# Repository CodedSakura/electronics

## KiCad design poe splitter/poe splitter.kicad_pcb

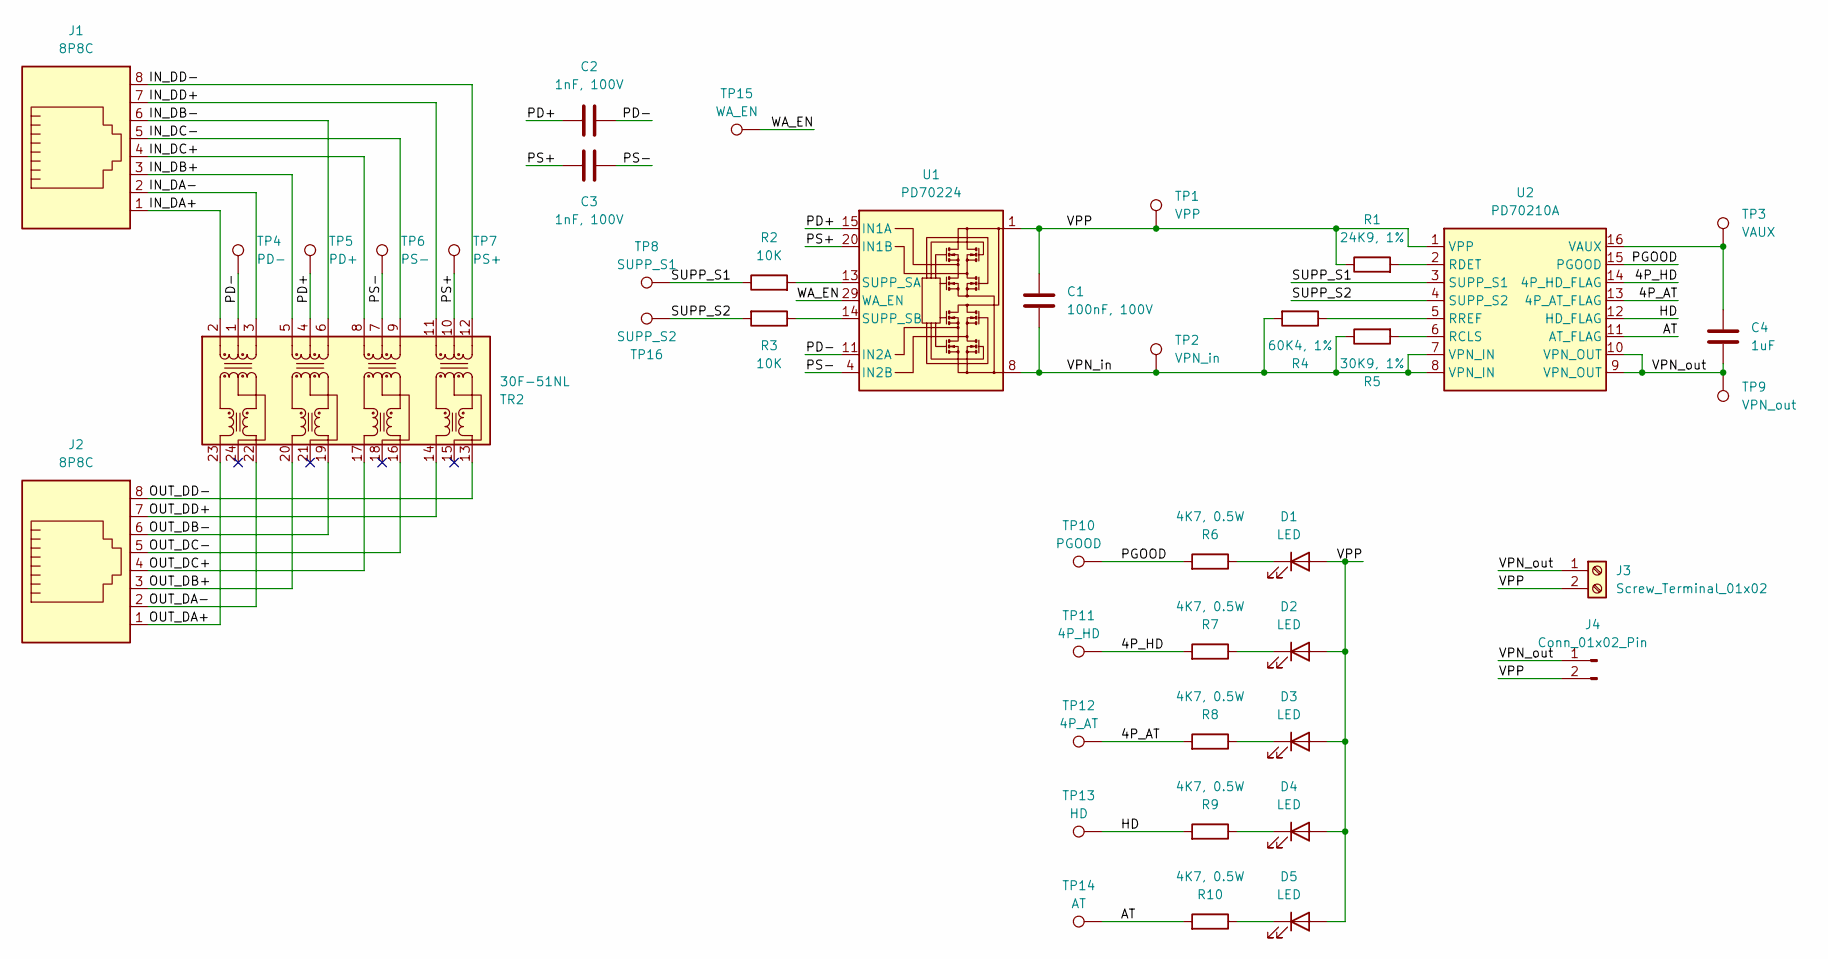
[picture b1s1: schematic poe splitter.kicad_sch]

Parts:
C1: 100nF, 100V; C_0805_2012Metric
C2, C3: 1nF, 100V; C_0805_2012Metric
C4: 1uF; C_0805_2012Metric
D1, D2, D3, D4, D5: LED; LED_0805_2012Metric
J1, J2: 8P8C; RJ45_Amphenol_54602-x08_Horizontal
J3: Screw_Terminal_01x02; TerminalBlock_Phoenix_MKDS-1,5-2_1x02_P5.00mm_Horizontal
J4: Conn_01x02_Pin; JST_VH_B2P-VH-B_1x02_P3.96mm_Vertical
R1: 24K9, 1%; R_0805_2012Metric
R2, R3: 10K; R_0805_2012Metric
R4: 60K4, 1%; R_0805_2012Metric
R5: 30K9, 1%; R_0805_2012Metric
R6, R7, R8, R9, R10: 4K7, 0.5W; R_0805_2012Metric
TP1: VPP; TestPoint_THTPad_1.0x1.0mm_Drill0.5mm
TP2: VPN_in; TestPoint_THTPad_1.0x1.0mm_Drill0.5mm
TP3: VAUX; TestPoint_THTPad_1.0x1.0mm_Drill0.5mm
TP4: PD-; TestPoint_THTPad_1.0x1.0mm_Drill0.5mm
TP5: PD+; TestPoint_THTPad_1.0x1.0mm_Drill0.5mm
TP6: PS-; TestPoint_THTPad_1.0x1.0mm_Drill0.5mm
TP7: PS+; TestPoint_THTPad_1.0x1.0mm_Drill0.5mm
TP8: SUPP_S1; TestPoint_THTPad_1.0x1.0mm_Drill0.5mm
TP9: VPN_out; TestPoint_THTPad_1.0x1.0mm_Drill0.5mm
TP10: PGOOD; TestPoint_THTPad_1.0x1.0mm_Drill0.5mm
TP11: 4P_HD; TestPoint_THTPad_1.0x1.0mm_Drill0.5mm
TP12: 4P_AT; TestPoint_THTPad_1.0x1.0mm_Drill0.5mm
TP13: HD; TestPoint_THTPad_1.0x1.0mm_Drill0.5mm
TP14: AT; TestPoint_THTPad_1.0x1.0mm_Drill0.5mm
TP15: WA_EN; TestPoint_THTPad_1.0x1.0mm_Drill0.5mm
TP16: SUPP_S2; TestPoint_THTPad_1.0x1.0mm_Drill0.5mm
TR2: 30F-51NL; Transformer_Ethernet_YDS_30F-51NL_SO-24_7.1x15.1mm
U1: PD70224; Microsemi_QFN-40-32-2EP_6x8mm_P0.5mm
U2: PD70210A; PD70210

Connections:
/4P_AT: R8.2, TP12.1, U2.13 (4P_AT_FLAG)
/4P_HD: R7.2, TP11.1, U2.14 (4P_HD_FLAG)
/AT: R10.2, TP14.1, U2.11 (AT_FLAG)
/HD: R9.2, TP13.1, U2.12 (HD_FLAG)
/IN_DA+: J1.1, TR2.2 (TD1+)
/IN_DA-: J1.2, TR2.3 (TD1-)
/IN_DB+: J1.3, TR2.5 (TD2+)
/IN_DB-: J1.6, TR2.6 (TD2-)
/IN_DC+: J1.4, TR2.8 (TD3+)
/IN_DC-: J1.5, TR2.9 (TD3-)
/IN_DD+: J1.7, TR2.11 (TD4+)
/IN_DD-: J1.8, TR2.12 (TD4-)
/OUT_DA+: J2.1, TR2.23 (MX1+)
/OUT_DA-: J2.2, TR2.22 (MX1-)
/OUT_DB+: J2.3, TR2.20 (MX2+)
/OUT_DB-: J2.6, TR2.19 (MX2-)
/OUT_DC+: J2.4, TR2.17 (MX3+)
/OUT_DC-: J2.5, TR2.16 (MX3-)
/OUT_DD+: J2.7, TR2.14 (MX4+)
/OUT_DD-: J2.8, TR2.13 (MX4-)
/PD+: C2.1, TP5.1, TR2.4 (CT), U1.15 (IN1A), U1.16 (IN1A), U1.27 (IN1A), U1.28 (IN1A)
/PD-: C2.2, TP4.1, TR2.1 (CT), U1.11 (IN2A), U1.12 (IN2A), U1.31 (IN2A), U1.32 (IN2A)
/PGOOD: R6.2, TP10.1, U2.15 (PGOOD)
/PS+: C3.1, TP7.1, TR2.10 (CT), U1.20 (IN1B), U1.21 (IN1B), U1.22 (IN1B), U1.23 (IN1B)
/PS-: C3.2, TP6.1, TR2.7 (CT), U1.4 (IN2B), U1.5 (IN2B), U1.6 (IN2B), U1.7 (IN2B)
/SUPP_S1: R2.1, TP8.1, U2.3 (SUPP_S1)
/SUPP_S2: R3.2, TP16.1, U2.4 (SUPP_S2)
/VPN_in: C1.2, R4.2, R5.1, TP2.1, U1.8, U1.9, U1.10, U1.17, U1.18, U1.19, U1.34, U2.7 (VPN_IN), U2.8 (VPN_IN)
/VPN_out: C4.2, J3.1, J4.1, TP9.1, U2.9 (VPN_OUT), U2.10 (VPN_OUT)
/VPP: C1.1, D1.2 (A), D2.2 (A), D3.2 (A), D4.2 (A), D5.2 (A), J3.2, J4.2, R1.1, TP1.1, U1.1, U1.2, U1.3, U1.24, U1.25, U1.26, U1.33, U2.1 (VPP)
/WA_EN: TP15.1, U1.29 (WA_EN)
unnamed: D1.1 (K), R6.1
unnamed: D2.1 (K), R7.1
unnamed: D3.1 (K), R8.1
unnamed: D4.1 (K), R9.1
unnamed: D5.1 (K), R10.1
unnamed: R2.2, U1.13 (SUPP_SA)
unnamed: R3.1, U1.14 (SUPP_SB)
unnamed: R5.2, U2.6 (RCLS)
unnamed: R1.2, U2.2 (RDET)
unnamed: R4.1, U2.5 (RREF)
unnamed: C4.1, TP3.1, U2.16 (VAUX)

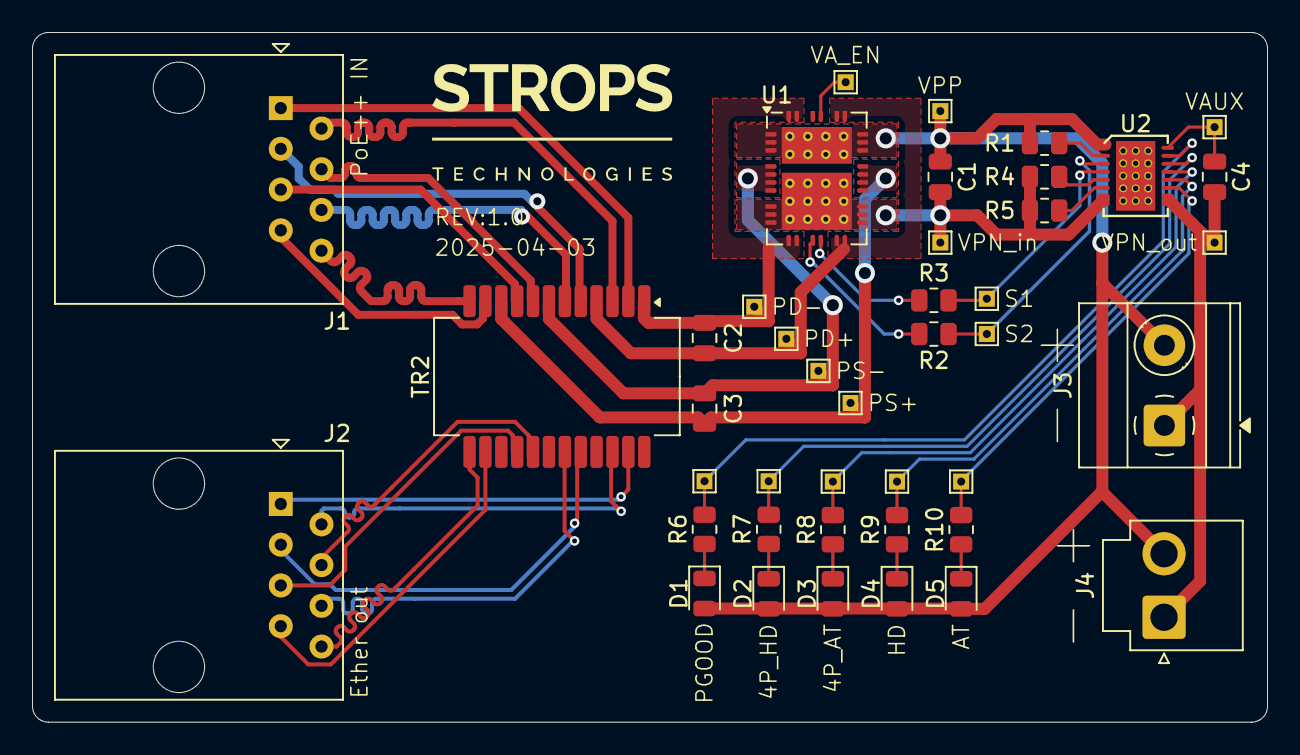
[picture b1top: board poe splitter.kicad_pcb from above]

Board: 2 copper layers, 77.0 x 43.0 mm, 42 parts (0 on the bottom side), 42 nets.

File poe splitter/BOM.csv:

Id+ADs-Designator+ADs-Footprint+ADs-Quantity+ADs-Designation+ADs-Supplier and ref+ADs-Price
1+ADs-C1+ADs-C+AF8-0805+AF8-2012Metric+ADs-1+ADs-100nF, 100V+ADs-JLCPCB C28233+ADs-
2+ADs-TP11+ADs-TestPoint+AF8-THTPad+AF8-1.0x1.0mm+AF8-Drill0.5mm+ADs-1+ADs-4P+AF8-HD+ADs-+AC0-+ADs-
3+ADs-R4+ADs-R+AF8-0805+AF8-2012Metric+ADs-1+ADs-60K4, 1+ACU-+ADs-JLCPCB C3016873+ADs-
4+ADs-J4+ADs-JST+AF8-VH+AF8-B2P+AC0-VH+AC0-B+AF8-1x02+AF8-P3.96mm+AF8-Vertical+ADs-1+ADs-Conn+AF8-01x02+AF8-Pin+ADs-JLCPCB C160315+ADs-
5+ADs-TR2+ADs-Transformer+AF8-Ethernet+AF8-YDS+AF8-30F+AC0-51NL+AF8-SO+AC0-24+AF8-7.1x15.1mm+ADs-1+ADs-30F+AC0-51NL+ADs-JLCPCB C123168+ADs-
6+ADs-R7,R8,R6,R10,R9+ADs-R+AF8-0805+AF8-2012Metric+ADs-5+ADs-4K7, 0.5W+ADs-JLCPCB C313926+ADs-
7+ADs-C4+ADs-C+AF8-0805+AF8-2012Metric+ADs-1+ADs-1uF+ADs-JLCPCB C105952+ADs-
8+ADs-D3,D4,D2,D5,D1+ADs-LED+AF8-0805+AF8-2012Metric+ADs-5+ADs-LED+ADs-JLCPCB C94741+ADs-
9+ADs-TP12+ADs-TestPoint+AF8-THTPad+AF8-1.0x1.0mm+AF8-Drill0.5mm+ADs-1+ADs-4P+AF8-AT+ADs-+AC0-+ADs-
10+ADs-U1+ADs-Microsemi+AF8-QFN+AC0-40+AC0-32+AC0-2EP+AF8-6x8mm+AF8-P0.5mm+ADs-1+ADs-PD70224+ADs-mouser 494+AC0-PD70224ILQ+AC0-TR+ADs-
11+ADs-J1,J2+ADs-RJ45+AF8-Amphenol+AF8-54602+AC0-x08+AF8-Horizontal+ADs-2+ADs-8P8C+ADs-mouser 649+AC0-54602+AC0-910LF+ADs-
12+ADs-R2,R3+ADs-R+AF8-0805+AF8-2012Metric+ADs-2+ADs-10K+ADs-JLCPCB C17414+ADs-
13+ADs-TP10+ADs-TestPoint+AF8-THTPad+AF8-1.0x1.0mm+AF8-Drill0.5mm+ADs-1+ADs-PGOOD+ADs-+AC0-+ADs-
14+ADs-TP7+ADs-TestPoint+AF8-THTPad+AF8-1.0x1.0mm+AF8-Drill0.5mm+ADs-1+ADs-PS+ADs-+AC0-+ADs-
15+ADs-J3+ADs-TerminalBlock+AF8-Phoenix+AF8-MKDS+AC0-1,5+AC0-2+AF8-1x02+AF8-P5.00mm+AF8-Horizontal+ADs-1+ADs-Screw+AF8-Terminal+AF8-01x02+ADs-mouser 651+AC0-1935161 +ADs-
16+ADs-TP3+ADs-TestPoint+AF8-THTPad+AF8-1.0x1.0mm+AF8-Drill0.5mm+ADs-1+ADs-VAUX+ADs-+AC0-+ADs-
17+ADs-TP9+ADs-TestPoint+AF8-THTPad+AF8-1.0x1.0mm+AF8-Drill0.5mm+ADs-1+ADs-VPN+AF8-out+ADs-+AC0-+ADs-
18+ADs-TP15+ADs-TestPoint+AF8-THTPad+AF8-1.0x1.0mm+AF8-Drill0.5mm+ADs-1+ADs-WA+AF8-EN+ADs-+AC0-+ADs-
19+ADs-TP5+ADs-TestPoint+AF8-THTPad+AF8-1.0x1.0mm+AF8-Drill0.5mm+ADs-1+ADs-PD+ADs-+AC0-+ADs-
20+ADs-R5+ADs-R+AF8-0805+AF8-2012Metric+ADs-1+ADs-30K9, 1+ACU-+ADs-JLCPCB C3016777+ADs-
21+ADs-U2+ADs-PD70210+ADs-1+ADs-PD70210A+ADs-mouser 494+AC0-PD70210AILD+AC0-TR+ADs-
22+ADs-R1+ADs-R+AF8-0805+AF8-2012Metric+ADs-1+ADs-24K9, 1+ACU-+ADs-JLCPCB C228658+ADs-
23+ADs-C3,C2+ADs-C+AF8-0805+AF8-2012Metric+ADs-2+ADs-1nF, 100V+ADs-JLCPCB C15177+ADs-
24+ADs-TP16+ADs-TestPoint+AF8-THTPad+AF8-1.0x1.0mm+AF8-Drill0.5mm+ADs-1+ADs-SUPP+AF8-S2+ADs-+AC0-+ADs-
25+ADs-TP8+ADs-TestPoint+AF8-THTPad+AF8-1.0x1.0mm+AF8-Drill0.5mm+ADs-1+ADs-SUPP+AF8-S1+ADs-+AC0-+ADs-
26+ADs-TP6+ADs-TestPoint+AF8-THTPad+AF8-1.0x1.0mm+AF8-Drill0.5mm+ADs-1+ADs-PS+AC0-+ADs-+AC0-+ADs-
27+ADs-TP1+ADs-TestPoint+AF8-THTPad+AF8-1.0x1.0mm+AF8-Drill0.5mm+ADs-1+ADs-VPP+ADs-+AC0-+ADs-
28+ADs-TP13+ADs-TestPoint+AF8-THTPad+AF8-1.0x1.0mm+AF8-Drill0.5mm+ADs-1+ADs-HD+ADs-+AC0-+ADs-
29+ADs-TP2+ADs-TestPoint+AF8-THTPad+AF8-1.0x1.0mm+AF8-Drill0.5mm+ADs-1+ADs-VPN+AF8-in+ADs-+AC0-+ADs-
30+ADs-TP14+ADs-TestPoint+AF8-THTPad+AF8-1.0x1.0mm+AF8-Drill0.5mm+ADs-1+ADs-AT+ADs-+AC0-+ADs-
31+ADs-TP4+ADs-TestPoint+AF8-THTPad+AF8-1.0x1.0mm+AF8-Drill0.5mm+ADs-1+ADs-PD+AC0-+ADs-+AC0-+ADs-

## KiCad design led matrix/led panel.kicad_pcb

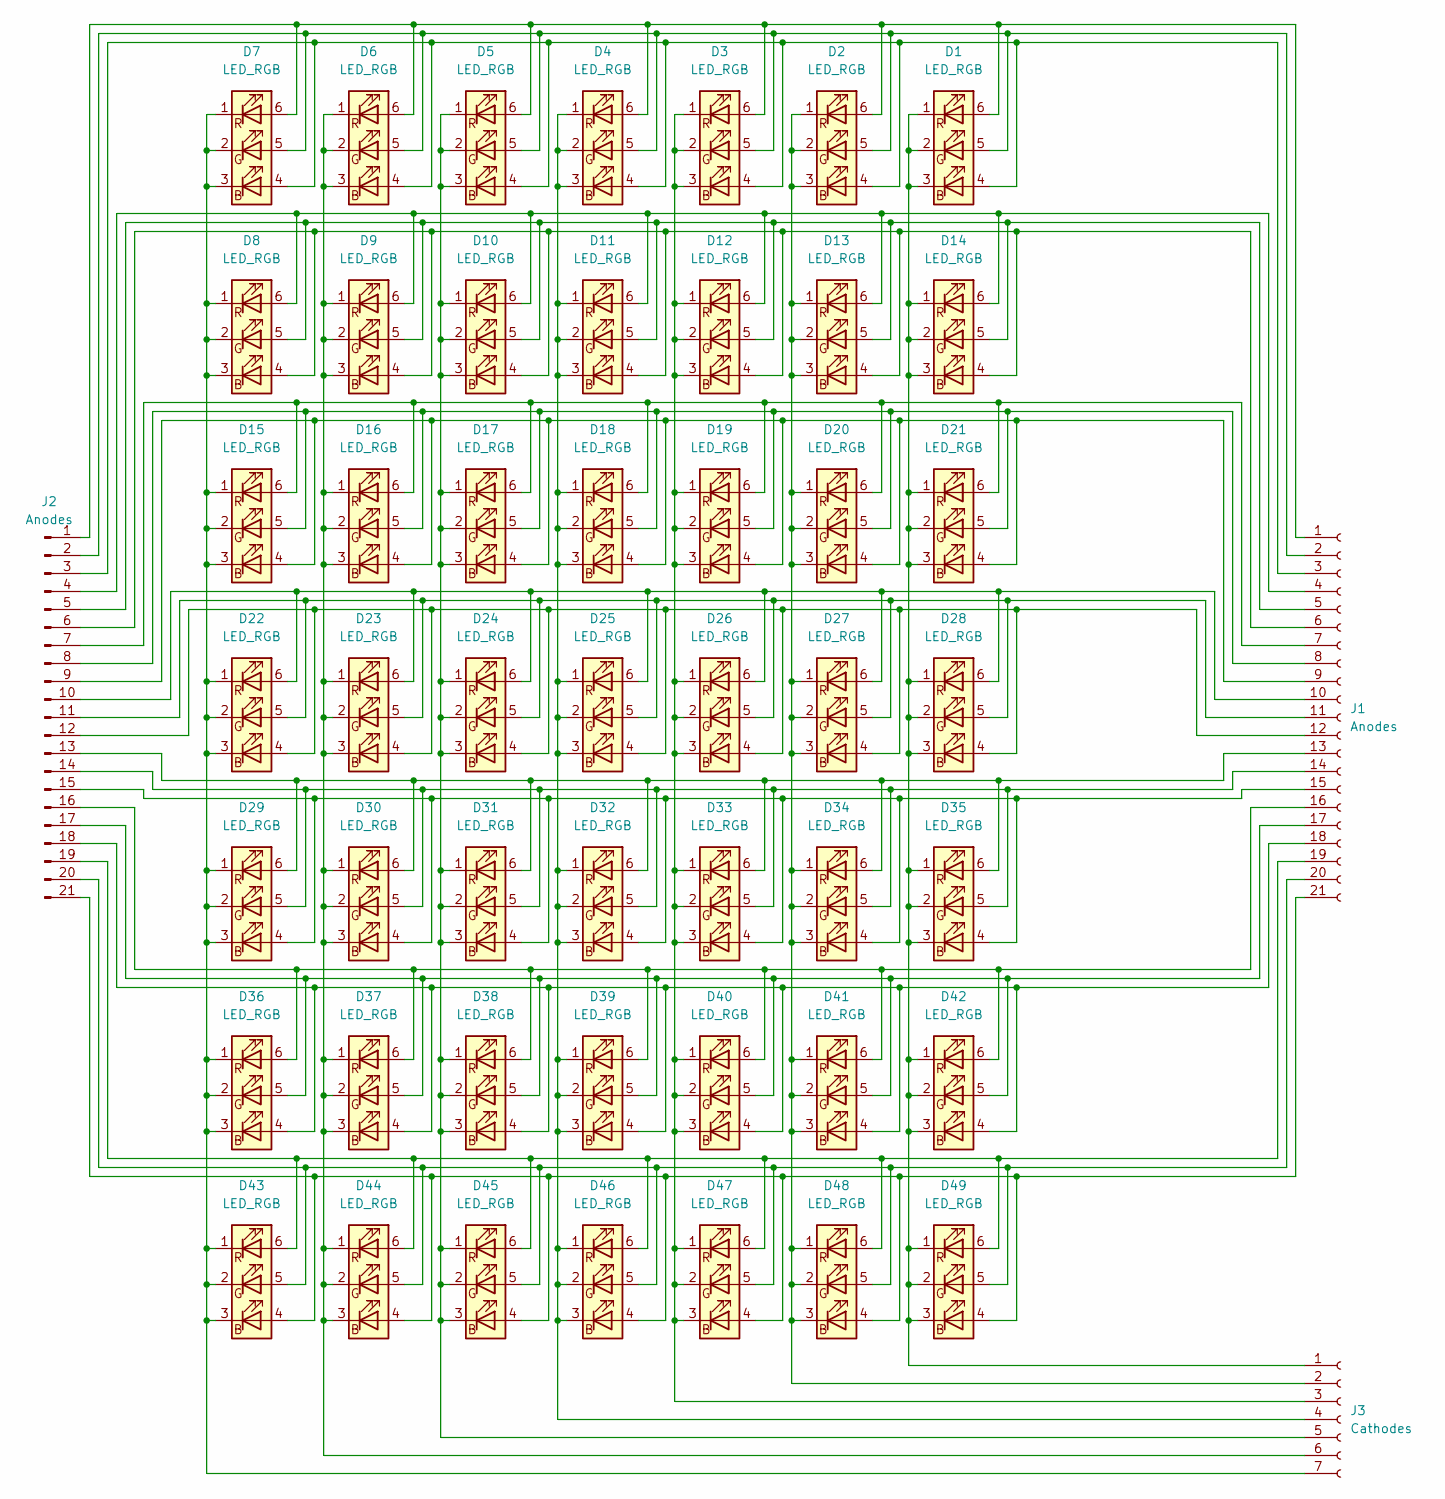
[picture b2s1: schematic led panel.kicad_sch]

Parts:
D1, D2, D3, D4, D5, D6, D7, D8, D9, D10, D11, D12, D13, D14, D15, D16, D17, D18, D19, D20, D21, D22, D23, D24, D25, D26, D27, D28, D29, D30, D31, D32, D33, D34, D35, D36, D37, D38, D39, D40, D41, D42, D43, D44, D45, D46, D47, D48, D49: LED_RGB; LED_RGB_5050-6
J1, J2: Anodes; Pin_1x21_P1.00mm_SMD
J3: Cathodes; Molex_200528-0070_1x07-1MP_P1.00mm_Horizontal

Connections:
unnamed: D1.4 (BA), D2.4 (BA), D3.4 (BA), D4.4 (BA), D5.4 (BA), D6.4 (BA), D7.4 (BA), J1.3, J2.3
unnamed: D1.1 (RK), D1.2 (GK), D1.3 (BK), D14.1 (RK), D14.2 (GK), D14.3 (BK), D21.1 (RK), D21.2 (GK), D21.3 (BK), D28.1 (RK), D28.2 (GK), D28.3 (BK), D35.1 (RK), D35.2 (GK), D35.3 (BK), D42.1 (RK), D42.2 (GK), D42.3 (BK), D49.1 (RK), D49.2 (GK), D49.3 (BK), J3.1
unnamed: D1.5 (GA), D2.5 (GA), D3.5 (GA), D4.5 (GA), D5.5 (GA), D6.5 (GA), D7.5 (GA), J1.2, J2.2
unnamed: D1.6 (RA), D2.6 (RA), D3.6 (RA), D4.6 (RA), D5.6 (RA), D6.6 (RA), D7.6 (RA), J1.1, J2.1
unnamed: D8.4 (BA), D9.4 (BA), D10.4 (BA), D11.4 (BA), D12.4 (BA), D13.4 (BA), D14.4 (BA), J1.6, J2.6
unnamed: D5.1 (RK), D5.2 (GK), D5.3 (BK), D10.1 (RK), D10.2 (GK), D10.3 (BK), D17.1 (RK), D17.2 (GK), D17.3 (BK), D24.1 (RK), D24.2 (GK), D24.3 (BK), D31.1 (RK), D31.2 (GK), D31.3 (BK), D38.1 (RK), D38.2 (GK), D38.3 (BK), D45.1 (RK), D45.2 (GK), D45.3 (BK), J3.5
unnamed: D8.5 (GA), D9.5 (GA), D10.5 (GA), D11.5 (GA), D12.5 (GA), D13.5 (GA), D14.5 (GA), J1.5, J2.5
unnamed: D8.6 (RA), D9.6 (RA), D10.6 (RA), D11.6 (RA), D12.6 (RA), D13.6 (RA), D14.6 (RA), J1.4, J2.4
unnamed: D4.1 (RK), D4.2 (GK), D4.3 (BK), D11.1 (RK), D11.2 (GK), D11.3 (BK), D18.1 (RK), D18.2 (GK), D18.3 (BK), D25.1 (RK), D25.2 (GK), D25.3 (BK), D32.1 (RK), D32.2 (GK), D32.3 (BK), D39.1 (RK), D39.2 (GK), D39.3 (BK), D46.1 (RK), D46.2 (GK), D46.3 (BK), J3.4
unnamed: D3.1 (RK), D3.2 (GK), D3.3 (BK), D12.1 (RK), D12.2 (GK), D12.3 (BK), D19.1 (RK), D19.2 (GK), D19.3 (BK), D26.1 (RK), D26.2 (GK), D26.3 (BK), D33.1 (RK), D33.2 (GK), D33.3 (BK), D40.1 (RK), D40.2 (GK), D40.3 (BK), D47.1 (RK), D47.2 (GK), D47.3 (BK), J3.3
unnamed: D2.1 (RK), D2.2 (GK), D2.3 (BK), D13.1 (RK), D13.2 (GK), D13.3 (BK), D20.1 (RK), D20.2 (GK), D20.3 (BK), D27.1 (RK), D27.2 (GK), D27.3 (BK), D34.1 (RK), D34.2 (GK), D34.3 (BK), D41.1 (RK), D41.2 (GK), D41.3 (BK), D48.1 (RK), D48.2 (GK), D48.3 (BK), J3.2
unnamed: D15.4 (BA), D16.4 (BA), D17.4 (BA), D18.4 (BA), D19.4 (BA), D20.4 (BA), D21.4 (BA), J1.9, J2.9
unnamed: D7.1 (RK), D7.2 (GK), D7.3 (BK), D8.1 (RK), D8.2 (GK), D8.3 (BK), D15.1 (RK), D15.2 (GK), D15.3 (BK), D22.1 (RK), D22.2 (GK), D22.3 (BK), D29.1 (RK), D29.2 (GK), D29.3 (BK), D36.1 (RK), D36.2 (GK), D36.3 (BK), D43.1 (RK), D43.2 (GK), D43.3 (BK), J3.7
unnamed: D15.5 (GA), D16.5 (GA), D17.5 (GA), D18.5 (GA), D19.5 (GA), D20.5 (GA), D21.5 (GA), J1.8, J2.8
unnamed: D15.6 (RA), D16.6 (RA), D17.6 (RA), D18.6 (RA), D19.6 (RA), D20.6 (RA), D21.6 (RA), J1.7, J2.7
unnamed: D6.1 (RK), D6.2 (GK), D6.3 (BK), D9.1 (RK), D9.2 (GK), D9.3 (BK), D16.1 (RK), D16.2 (GK), D16.3 (BK), D23.1 (RK), D23.2 (GK), D23.3 (BK), D30.1 (RK), D30.2 (GK), D30.3 (BK), D37.1 (RK), D37.2 (GK), D37.3 (BK), D44.1 (RK), D44.2 (GK), D44.3 (BK), J3.6
unnamed: D22.4 (BA), D23.4 (BA), D24.4 (BA), D25.4 (BA), D26.4 (BA), D27.4 (BA), D28.4 (BA), J1.12, J2.12
unnamed: D22.5 (GA), D23.5 (GA), D24.5 (GA), D25.5 (GA), D26.5 (GA), D27.5 (GA), D28.5 (GA), J1.11, J2.11
unnamed: D22.6 (RA), D23.6 (RA), D24.6 (RA), D25.6 (RA), D26.6 (RA), D27.6 (RA), D28.6 (RA), J1.10, J2.10
unnamed: D29.4 (BA), D30.4 (BA), D31.4 (BA), D32.4 (BA), D33.4 (BA), D34.4 (BA), D35.4 (BA), J1.15, J2.15
unnamed: D29.5 (GA), D30.5 (GA), D31.5 (GA), D32.5 (GA), D33.5 (GA), D34.5 (GA), D35.5 (GA), J1.14, J2.14
unnamed: D29.6 (RA), D30.6 (RA), D31.6 (RA), D32.6 (RA), D33.6 (RA), D34.6 (RA), D35.6 (RA), J1.13, J2.13
unnamed: D36.4 (BA), D37.4 (BA), D38.4 (BA), D39.4 (BA), D40.4 (BA), D41.4 (BA), D42.4 (BA), J1.18, J2.18
unnamed: D36.5 (GA), D37.5 (GA), D38.5 (GA), D39.5 (GA), D40.5 (GA), D41.5 (GA), D42.5 (GA), J1.17, J2.17
unnamed: D36.6 (RA), D37.6 (RA), D38.6 (RA), D39.6 (RA), D40.6 (RA), D41.6 (RA), D42.6 (RA), J1.16, J2.16
unnamed: D43.4 (BA), D44.4 (BA), D45.4 (BA), D46.4 (BA), D47.4 (BA), D48.4 (BA), D49.4 (BA), J1.21, J2.21
unnamed: D43.5 (GA), D44.5 (GA), D45.5 (GA), D46.5 (GA), D47.5 (GA), D48.5 (GA), D49.5 (GA), J1.20, J2.20
unnamed: D43.6 (RA), D44.6 (RA), D45.6 (RA), D46.6 (RA), D47.6 (RA), D48.6 (RA), D49.6 (RA), J1.19, J2.19

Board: 2 copper layers, 52 parts (3 on the bottom side), 28 nets, no tracks yet.

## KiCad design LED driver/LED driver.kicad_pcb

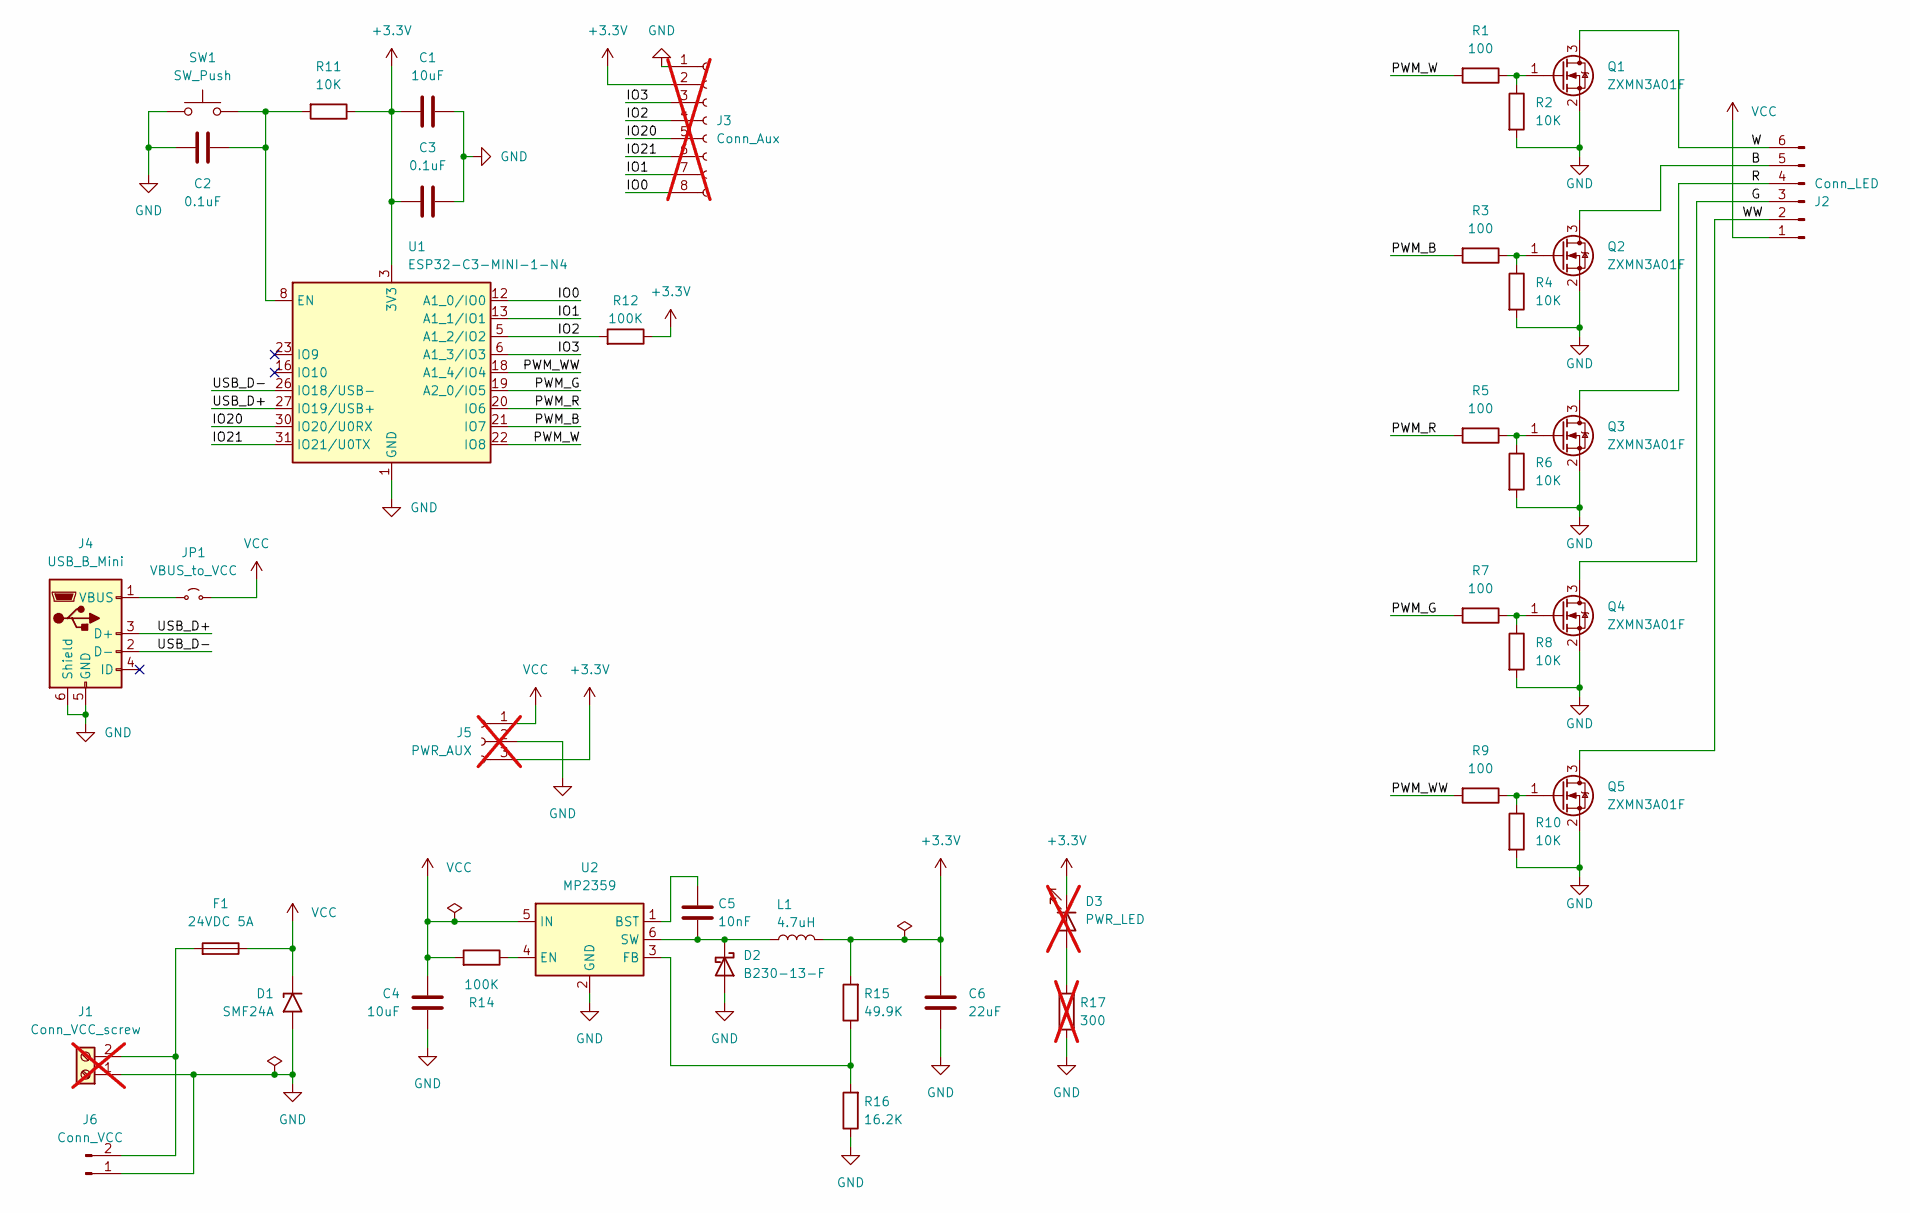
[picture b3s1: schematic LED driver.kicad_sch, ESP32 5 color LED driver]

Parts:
C1, C4: 10uF; C_0603_1608Metric
C2, C3: 0.1uF; C_0603_1608Metric
C5: 10nF; C_0603_1608Metric
C6: 22uF; C_0603_1608Metric
D1: SMF24A; D_SMF
D2: B230-13-F; D_SMB
D3: PWR_LED; D_0603_1608Metric_Pad1.05x0.95mm_HandSolder; not fitted
F1: 24VDC 5A; Fuse_1206_3216Metric_Pad1.42x1.75mm_HandSolder
J1: Conn_VCC_screw; TerminalBlock_Phoenix_MKDS-1,5-2_1x02_P5.00mm_Horizontal; not fitted
J2: Conn_LED; JST_VH_B6PS-VH_1x06_P3.96mm_Horizontal
J3: Conn_Aux; PinSocket_2x04_P2.54mm_Vertical; not fitted
J4: USB_B_Mini; USB_Mini-B_AdamTech_MUSB-B5-S-VT-TSMT-1_SMD_Vertical
J5: PWR_AUX; PinHeader_1x03_P2.54mm_Vertical; not fitted
J6: Conn_VCC; JST_VH_B2PS-VH_1x02_P3.96mm_Horizontal
JP1: VBUS_to_VCC; PinHeader_1x02_P2.54mm_Vertical
L1: 4.7uH; L_1210_3225Metric
Q1, Q2, Q3, Q4, Q5: ZXMN3A01F; SOT-23
R1, R3, R5, R7, R9: 100; R_0603_1608Metric
R2, R4, R6, R8, R10, R11: 10K; R_0603_1608Metric
R12, R14: 100K; R_0603_1608Metric
R15: 49.9K; R_0603_1608Metric
R16: 16.2K; R_0603_1608Metric
R17: 300; R_0603_1608Metric_Pad0.98x0.95mm_HandSolder; not fitted
SW1: SW_Push; SW_SPST_B3U-1000P
U1: ESP32-C3-MINI-1-N4; ESP32C3MINI1N4; Mouser Part Number 356-ESP32-C3-MINI1N4
U2: MP2359; TSOT-23-6

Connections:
+3.3V: C1.2, C3.2, C6.1, D3.1 (K), J3.2, J5.3, L1.2, R11.1, R12.1, R15.2, U1.3 (3V3)
/B: J2.5, Q2.3 (D)
/G: J2.3, Q4.3 (D)
/IO0: J3.8, U1.12 (A1_0/IO0)
/IO1: J3.7, U1.13 (A1_1/IO1)
/IO2: J3.4, R12.2, U1.5 (A1_2/IO2)
/IO3: J3.3, U1.6 (A1_3/IO3)
/IO20: J3.5, U1.30 (IO20/U0RX)
/IO21: J3.6, U1.31 (IO21/U0TX)
/PWM_B: R3.2, U1.21 (IO7)
/PWM_G: R7.2, U1.19 (A2_0/IO5)
/PWM_R: R5.2, U1.20 (IO6)
/PWM_W: R1.2, U1.22 (IO8)
/PWM_WW: R9.2, U1.18 (A1_4/IO4)
/R: J2.4, Q3.3 (D)
/USB_D+: J4.3 (D+), U1.27 (IO19/USB+)
/USB_D-: J4.2 (D-), U1.26 (IO18/USB-)
/W: J2.6, Q1.3 (D)
/WW: J2.2, Q5.3 (D)
GND: C1.1, C2.1, C3.1, C4.2, C6.2, D1.2 (A2), D2.2 (A), J1.1, J3.1, J4.5 (GND), J4.6 (Shield), J5.2, J6.1, Q1.2 (S), Q2.2 (S), Q3.2 (S), Q4.2 (S), Q5.2 (S), R2.2, R4.2, R6.2, R8.2, R10.2, R16.1, R17.1, SW1.1, U1.1 (GND), U1.2 (GND_2), U1.11 (GND_3), U1.14 (GND_4), U1.36 (GND_5), U1.37 (GND_6), U1.38 (GND_7), U1.39 (GND_8), U1.40 (GND_9), U1.41 (GND_10), U1.42 (GND_11), U1.43 (GND_12), U1.44 (GND_13), U1.45 (GND_14), U1.46 (GND_15), U1.47 (GND_16), U1.48 (GND_17), U1.49 (GND_18), U1.50 (GND_19), U1.51 (GND_20), U1.52 (GND_21), U1.53 (GND_22), U1.54 (GND_23), U1.55 (GND_24), U1.56 (GND_25), U1.57 (GND_26), U1.58 (GND_27), U1.59 (GND_28), U1.60 (GND_29), U1.61 (GND_30), U2.2 (GND)
unnamed: C5.2, D2.1 (K), L1.1, U2.6 (SW)
unnamed: D3.2 (A), R17.2
unnamed: F1.2, J1.2, J6.2
unnamed: J4.1 (VBUS), JP1.1 (A)
unnamed: Q1.1 (G), R1.1, R2.1
unnamed: Q2.1 (G), R3.1, R4.1
unnamed: Q3.1 (G), R5.1, R6.1
unnamed: Q4.1 (G), R7.1, R8.1
unnamed: Q5.1 (G), R9.1, R10.1
unnamed: C2.2, R11.2, SW1.2, U1.8 (EN)
unnamed: C5.1, U2.1 (BST)
unnamed: R14.1, U2.4 (EN)
unnamed: R15.1, R16.2, U2.3 (FB)
VCC: C4.1, D1.1 (A1), F1.1, J2.1, J5.1, JP1.2 (B), R14.2, U2.5 (IN)

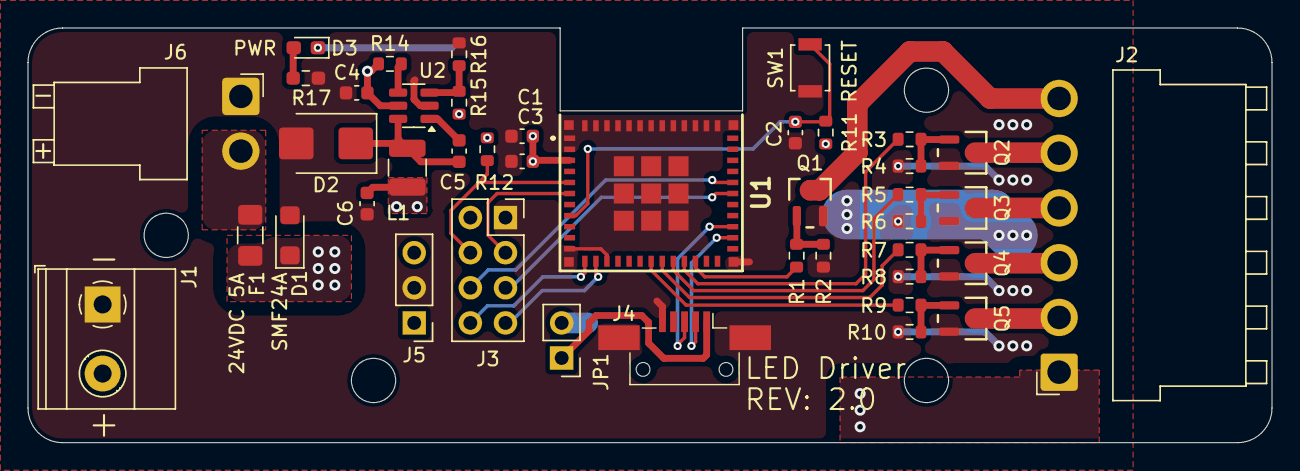
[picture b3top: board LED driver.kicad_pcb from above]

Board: 2 copper layers, 90.0 x 30.0 mm, 42 parts (0 on the bottom side), 34 nets.

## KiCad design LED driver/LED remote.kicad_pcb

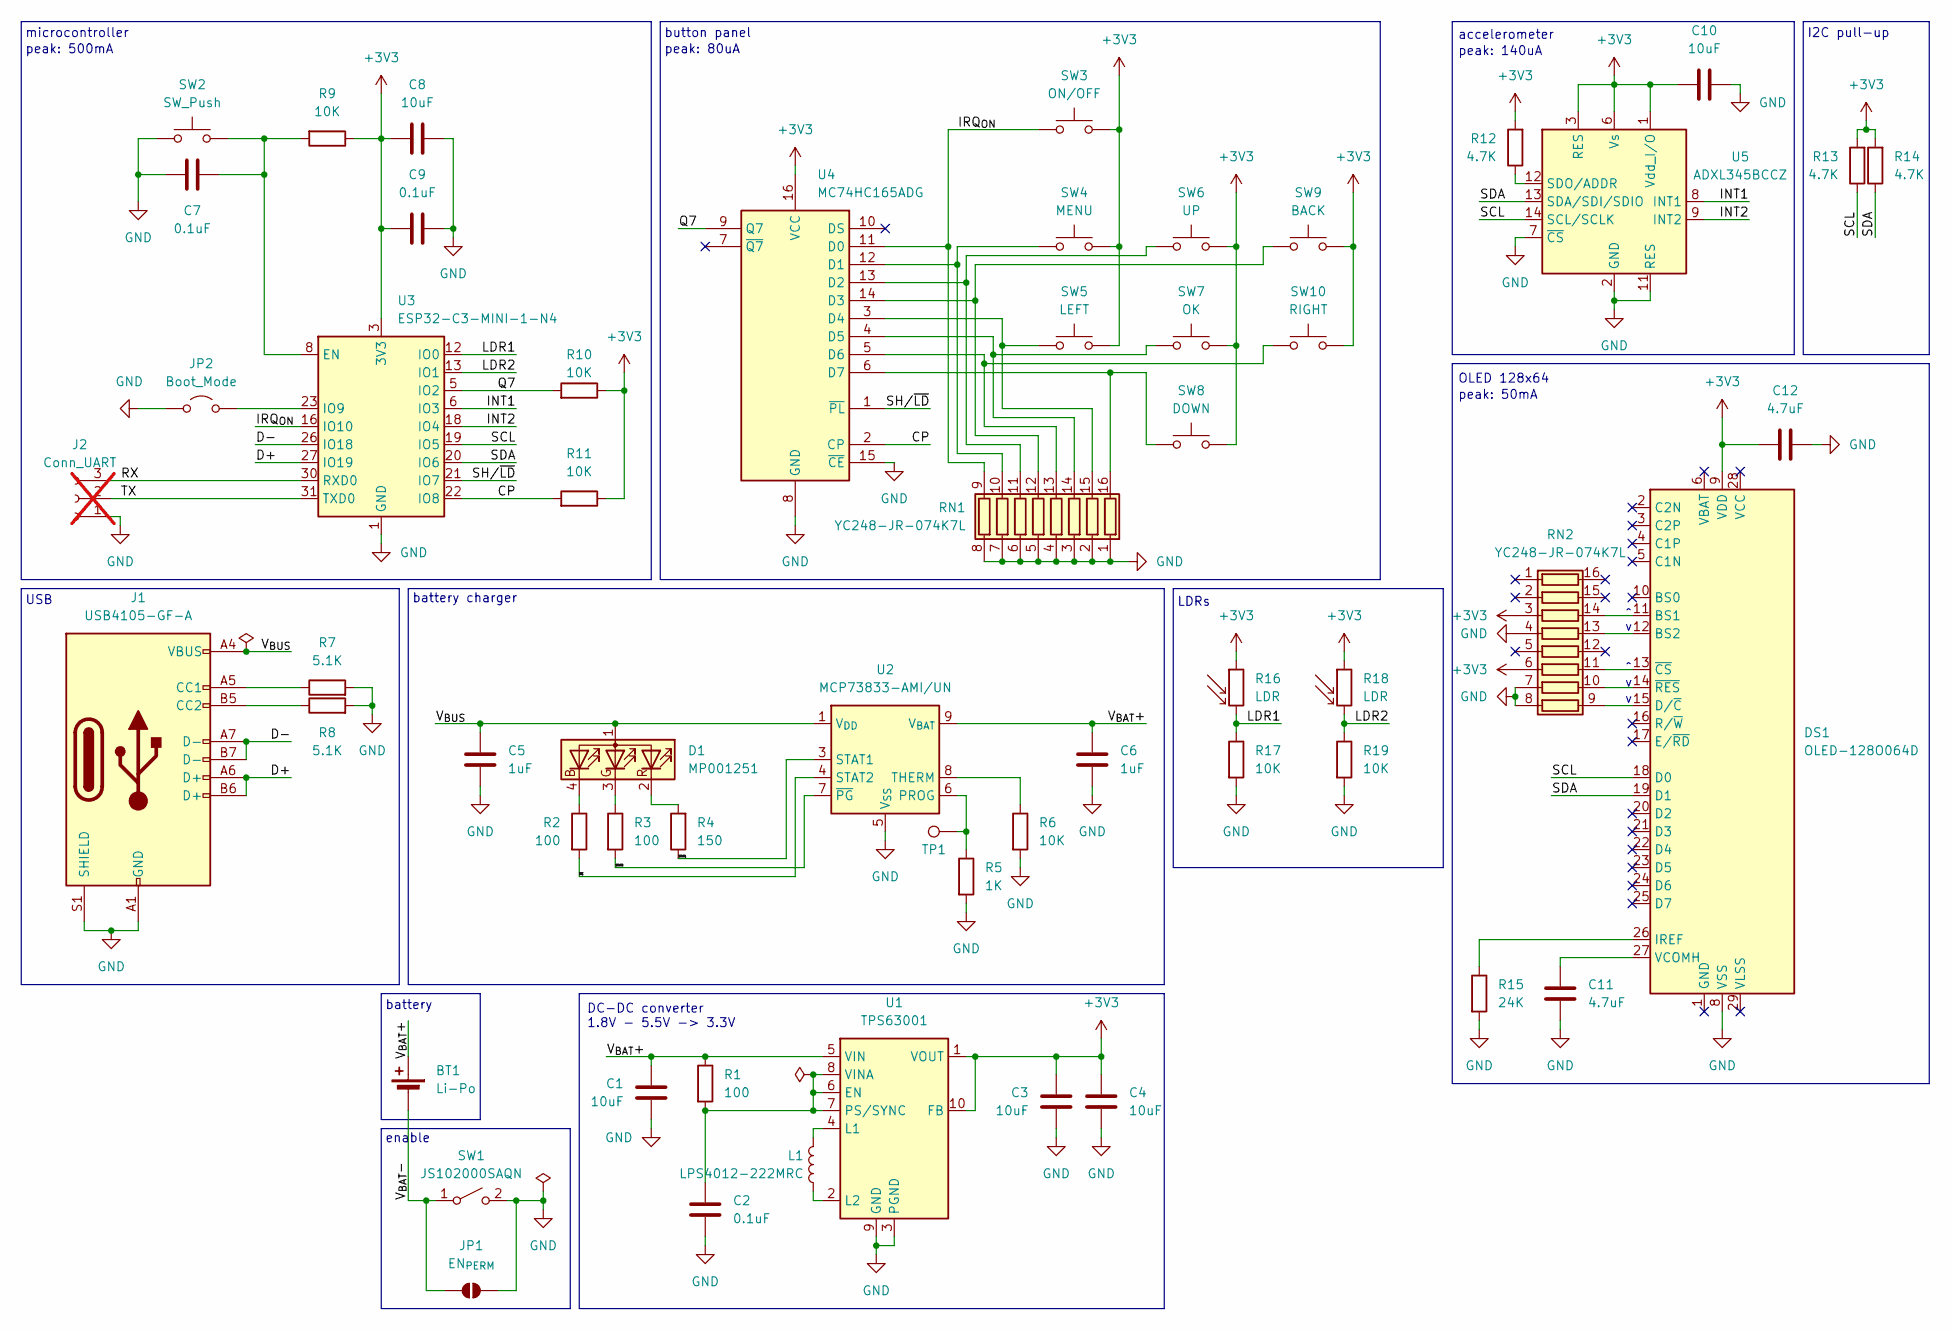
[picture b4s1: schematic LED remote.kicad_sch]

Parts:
BT1: Li-Po; S2BPHSM4TBLFSN
C1, C3, C4, C8, C10: 10uF; C_0603_1608Metric_Pad1.08x0.95mm_HandSolder
C2, C7, C9: 0.1uF; C_0603_1608Metric_Pad1.08x0.95mm_HandSolder
C5, C6: 1uF; C_0603_1608Metric_Pad1.08x0.95mm_HandSolder
C11, C12: 4.7uF; C_0603_1608Metric_Pad1.08x0.95mm_HandSolder
D1: MP001251; LED_MP001251_3.5x2.8mm
DS1: OLED-128O064D
J1: USB4105-GF-A; USB_C_Receptacle_GCT_USB4105-xx-A_16P_TopMnt_Horizontal
J2: Conn_UART; PinHeader_1x03_P1.00mm_Vertical_SMD_Pin1Left; not fitted
JP1: EN_{PERM}; SolderJumper-2_P1.3mm_Open_RoundedPad1.0x1.5mm
JP2: Boot_Mode; SolderJumper-2_P1.3mm_Open_TrianglePad1.0x1.5mm
L1: LPS4012-222MRC; L_Coilcraft_LPS4012
R1, R2, R3: 100; R_0603_1608Metric_Pad0.98x0.95mm_HandSolder
R4: 150; R_0603_1608Metric_Pad0.98x0.95mm_HandSolder
R5: 1K; R_0603_1608Metric_Pad0.98x0.95mm_HandSolder
R6, R9, R10, R11, R17, R19: 10K; R_0603_1608Metric_Pad0.98x0.95mm_HandSolder
R7, R8: 5.1K; R_0603_1608Metric_Pad0.98x0.95mm_HandSolder
R12, R13, R14: 4.7K; R_0603_1608Metric_Pad0.98x0.95mm_HandSolder
R15: 24K; R_0603_1608Metric_Pad0.98x0.95mm_HandSolder
R16, R18: LDR; R_LDR_5.0x4.1mm_P3mm_Vertical
RN1, RN2: YC248-JR-074K7L; RES_YC248_4X1P6_YAG
SW1: JS102000SAQN; SW_SPDT_CK_JS102011SAQN
SW2: SW_Push; SW_SPST_B3U-1000P
SW3: ON/OFF; SW_PUSH_6mm_H4.3mm
SW4: MENU; SW_PUSH_6mm_H4.3mm
SW5: LEFT; SW_PUSH_6mm_H4.3mm
SW6: UP; SW_PUSH_6mm_H4.3mm
SW7: OK; SW_PUSH_6mm_H4.3mm
SW8: DOWN; SW_PUSH_6mm_H4.3mm
SW9: BACK; SW_PUSH_6mm_H4.3mm
SW10: RIGHT; SW_PUSH_6mm_H4.3mm
TP1: TestPoint; TestPoint_Pad_D1.5mm
U1: TPS63001; Texas_DRC0010J_ThermalVias
U2: MCP73833-AMI/UN; MSOP-10_3x3mm_P0.5mm
U3: ESP32-C3-MINI-1-N4; ESP32C3MINI1N4; Mouser Part Number 356-ESP32-C3-MINI1N4
U4: MC74HC165ADG; SOIC-16_3.9x9.9mm_P1.27mm
U5: ADXL345BCCZ; LGA-14_3x5mm_P0.8mm_LayoutBorder1x6y

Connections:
+3V3: C3.1, C4.1, C8.2, C9.2, C10.1, C12.1, DS1.9 (VDD), R9.1, R10.1, R11.1, R12.2, R13.2, R14.2, R16.1, R18.1, RN2.3 (R2), RN2.6 (R5), SW3.2, SW4.2, SW5.2, SW6.2, SW7.2, SW8.2, SW9.2, SW10.2, U1.1 (VOUT), U1.10 (FB), U3.3 (3V3), U4.16 (VCC), U5.1 (Vdd_I/O), U5.3 (RES), U5.6 (Vs)
/CP: R11.2, U3.22 (IO8), U4.2 (CP)
/D+: J1.A6 (D+), J1.B6 (D+), U3.27 (IO19)
/D-: J1.A7 (D-), J1.B7 (D-), U3.26 (IO18)
/INT1: U3.6 (IO3), U5.8 (INT1)
/INT2: U3.18 (IO4), U5.9 (INT2)
/IRQ_{ON}: RN1.9 (R8), SW3.1, U3.16 (IO10), U4.11 (D0)
/LDR1: R16.2, R17.1, U3.12 (IO0)
/LDR2: R18.2, R19.1, U3.13 (IO1)
/Q7: R10.2, U3.5 (IO2), U4.9 (Q7)
/RX: J2.3, U3.30 (RXD0)
/SCL: DS1.18 (D0), R13.1, U3.19 (IO5), U5.14 (SCL/SCLK)
/SDA: DS1.19 (D1), R14.1, U3.20 (IO6), U5.13 (SDA/SDI/SDIO)
/SH/~LD: U3.21 (IO7), U4.1 (~PL)
/STAT1: R4.1, U2.3 (STAT1)
/STAT2: R3.2, U2.7 (~PG)
/TX: J2.2, U3.31 (TXD0)
/V_{BAT}+: BT1.1 (+), C1.1, C6.1, R1.1, U1.5 (VIN), U2.9 (V_{BAT}), U2.10 (V_{BAT})
/V_{BAT}-: BT1.2 (-), JP1.1 (A), SW1.1 (A)
/V_{BUS}: C5.1, D1.1 (A), J1.A4 (VBUS), J1.A9 (VBUS), J1.B4 (VBUS), J1.B9 (VBUS), U2.1 (V_{DD}), U2.2 (V_{DD})
/~PG: R2.2, U2.4 (STAT2)
GND: C1.2, C2.2, C3.2, C4.2, C5.2, C6.2, C7.1, C8.1, C9.1, C10.2, C11.1, C12.2, DS1.8 (VSS), J1.A1 (GND), J1.A12 (GND), J1.B1 (GND), J1.B12 (GND), J1.S1 (SHIELD), J2.1, JP1.2 (B), JP2.2 (B), R5.2, R6.2, R7.2, R8.2, R15.2, R17.2, R19.2, RN1.1 (common), RN1.2 (R1), RN1.3 (R2), RN1.4 (R3), RN1.5 (R4), RN1.6 (R5), RN1.7 (R6), RN1.8 (R7), RN2.4 (R3), RN2.7 (R6), RN2.8 (R7), SW1.2 (B), SW2.1, U1.3 (PGND), U1.9 (GND), U1.11 (PGND), U2.5 (V_{SS}), U3.1 (GND), U3.2 (GND_2), U3.11 (GND_3), U3.14 (GND_4), U3.36 (GND_5), U3.37 (GND_6), U3.38 (GND_7), U3.39 (GND_8), U3.40 (GND_9), U3.41 (GND_10), U3.42 (GND_11), U3.43 (GND_12), U3.44 (GND_13), U3.45 (GND_14), U3.46 (GND_15), U3.47 (GND_16), U3.48 (GND_17), U3.49 (GND_18), U3.50 (GND_19), U3.51 (GND_20), U3.52 (GND_21), U3.53 (GND_22), U3.54 (GND_23), U3.55 (GND_24), U3.56 (GND_25), U3.57 (GND_26), U3.58 (GND_27), U3.59 (GND_28), U3.60 (GND_29), U3.61 (GND_30), U4.8 (GND), U4.15 (~CE), U5.2 (GND), U5.4 (GND), U5.5 (GND), U5.7 (~CS), U5.11 (RES)
unnamed: D1.4 (BK), R2.1
unnamed: D1.3 (GK), R3.1
unnamed: D1.2 (RK), R4.2
unnamed: DS1.11 (BS1), RN2.14 (R8)
unnamed: DS1.12 (BS2), RN2.13 (R8)
unnamed: DS1.15 (D/~C), RN2.9 (R8)
unnamed: DS1.26 (IREF), R15.1
unnamed: C11.2, DS1.27 (VCOMH)
unnamed: DS1.13 (~CS), RN2.11 (R8)
unnamed: DS1.14 (~RES), RN2.10 (R8)
unnamed: J1.A5 (CC1), R7.1
unnamed: J1.B5 (CC2), R8.1
unnamed: JP2.1 (A), U3.23 (IO9)
unnamed: C2.1, R1.2, U1.6 (EN), U1.7 (PS/SYNC), U1.8 (VINA)
unnamed: L1.1, U1.4 (L1)
unnamed: L1.2, U1.2 (L2)
unnamed: R5.1, TP1.1, U2.6 (PROG)
unnamed: R6.1, U2.8 (THERM)
unnamed: C7.2, R9.2, SW2.2, U3.8 (EN)
unnamed: RN1.10 (R8), SW4.1, U4.12 (D1)
unnamed: RN1.11 (R8), SW6.1, U4.13 (D2)
unnamed: RN1.12 (R8), SW9.1, U4.14 (D3)
unnamed: RN1.15 (R8), SW5.1, U4.3 (D4)
unnamed: RN1.14 (R8), SW7.1, U4.4 (D5)
unnamed: RN1.13 (R8), SW10.1, U4.5 (D6)
unnamed: RN1.16 (R8), SW8.1, U4.6 (D7)
unnamed: R12.1, U5.12 (SDO/ADDR)

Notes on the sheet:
battery charger
button panel
accelerometer
microcontroller
battery
peak: 140uA
peak: 50mA
OLED 128x64
USB
peak: 500mA
LDRs
DC-DC converter 1.8V - 5.5V -> 3.3V
enable
peak: 80uA
I2C pull-up
